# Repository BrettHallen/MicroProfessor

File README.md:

# Micro Professor MPF
The Multitech (Acer) Micro Professor MPF range of computers:

- MPF-I: Z80 trainer with six 7-digit display
- MPF-IA: Z80 trainer with six 7-digit display
- MPF-IB: Z80 trainer with six 7-digit display
- [MPF-IP: Z80 trainer with 20-digit VFD and QWERTY keyboard](/MPF-IP)
- MPF-I/88: 8088 trainer with 2x20 LCD
- MPF-II: 6502 Apple ][ clone with built-in keyboard
- [MPF-III: 6502 Apple //e clone with separate keyboard](/MPF-III)
- [MPF-PC/500: IBM PC/XT clone on an ISA card](/MPF-PC500)

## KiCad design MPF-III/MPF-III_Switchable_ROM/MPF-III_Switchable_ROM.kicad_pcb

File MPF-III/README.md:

# Multitech Micro Professor MPF-III
The MPF-III was Multitech's (later Acer) Apple //e clone, coming after the MPF-II Apple ][ clone.<br>

My example is a PAL model MPF-III/311.  The NTSC model is the MPF-III/310.<br>

Unfortunatley mine came without a keyboard which means it's not usable because:
- It's a custom keyboard using a serial protocol via a DE9 connector
- The schematics have been scrubbed from the Internet (Archive)
- You need a keyboard to do anything

I do know the DE9 interface pin out and am currently trying to reverse engineer the protocol.  I also know the scan codes and keyboard layout (but not keyboard matrix) from the available documentation.<br>

I do also have a dump of the MCS-48 firmware in the keyboard.<br>

My example actually has dual ROMs that can be switched: it has Multitech's original Apple clone firmware plus an almost exact copy of the Apple //e firmware.<br>

## [Documentation](/MPF-III/Documentation)
Copies of the MPF-III documentation (available on Archive) just in case they get disappeared from there:
- BASIC Programming Manual
- Operating Manual (working on trying to reduce my 190MB PDF copy)
- Reference Manual (working on trying to reduce my 190MB PDF copy)

## [Images](/MPF-III/Images)
Images of my MPF-III/311 machine's inards.

## [Keyboard](/MPF-III/Keyboard)
My in-progress attempt to develop a home brew replacement for the original Multitech keyboard.<br>

The keyboard looks to be similar to the Multitech AccuFeel so this is perhaps a possible replacment, if one of those could be found of course.

## [Switchable Firmware](/MPF-III/MPF-III_Switchable_ROM)
Small PCB to add the ability to switch between Multitech's original firmware (boots to "MPF-III") and the actual Apple //e firmware (boots to "APPLE ][".<br>

Takes two 27128 EPROMs (one for combined CD and one for combined EF) which are switched via the A13 address line.<br>

## [ROMs](/MPF-III/ROMs)
Dumps of the ROMs from my machine (MOS 1.3) and RetroAND's (MOS 1.1), plus also some analysis of the keyboard microcontroller code and maybe other parts that differ from a standard Apple IIe.<br>

A big thanks to [RetroAND and Retrolab](https://bitspassats.com/index.php/Main_Page) for getting the keyboard controller ROM dumped!

## [PALs](/MPF-III/PALs)
Dumps of the PALs courtesy of [RetroAND and Retrolab](https://bitspassats.com/index.php/Main_Page).

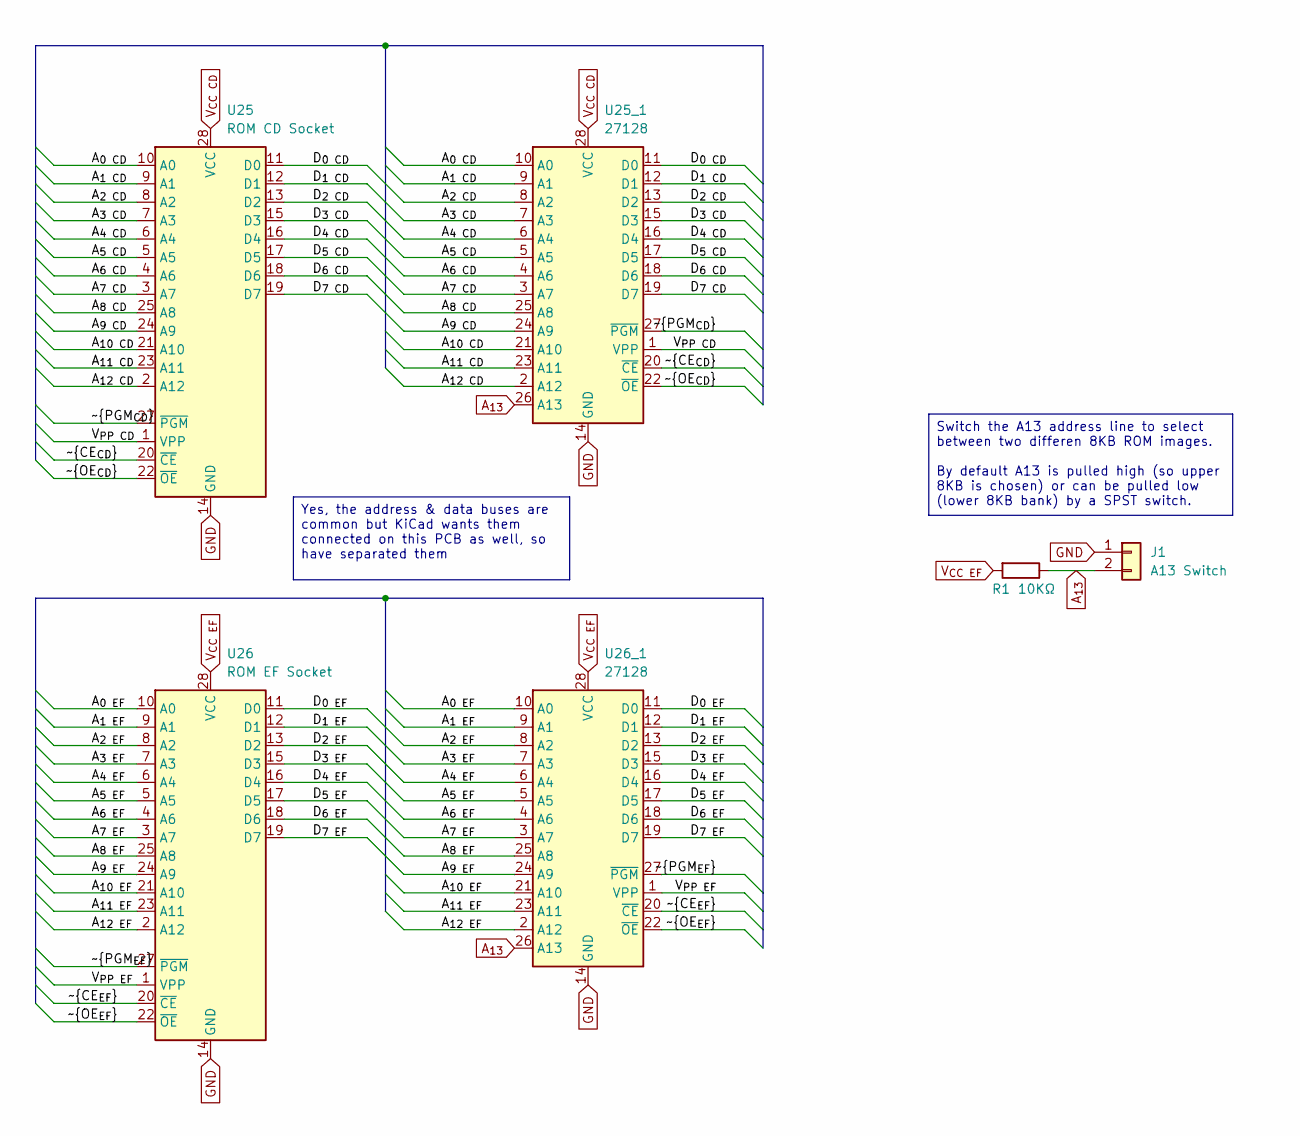
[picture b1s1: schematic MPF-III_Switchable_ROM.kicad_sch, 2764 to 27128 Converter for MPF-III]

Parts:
J1: A13 Switch; PinHeader_1x02_P2.54mm_Vertical
R1: 10KΩ; R_Axial_DIN0207_L6.3mm_D2.5mm_P7.62mm_Horizontal
U25: ROM CD Socket; DIP-28_Adapter
U25_1, U26_1: 27128; DIP-28_W15.24mm
U26: ROM EF Socket; DIP-28_Adapter

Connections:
/A_{0 CD}: U25.10 (A0), U25_1.10 (A0)
/A_{0 EF}: U26.10 (A0), U26_1.10 (A0)
/A_{1 CD}: U25.9 (A1), U25_1.9 (A1)
/A_{1 EF}: U26.9 (A1), U26_1.9 (A1)
/A_{2 CD}: U25.8 (A2), U25_1.8 (A2)
/A_{2 EF}: U26.8 (A2), U26_1.8 (A2)
/A_{3 CD}: U25.7 (A3), U25_1.7 (A3)
/A_{3 EF}: U26.7 (A3), U26_1.7 (A3)
/A_{4 CD}: U25.6 (A4), U25_1.6 (A4)
/A_{4 EF}: U26.6 (A4), U26_1.6 (A4)
/A_{5 CD}: U25.5 (A5), U25_1.5 (A5)
/A_{5 EF}: U26.5 (A5), U26_1.5 (A5)
/A_{6 CD}: U25.4 (A6), U25_1.4 (A6)
/A_{6 EF}: U26.4 (A6), U26_1.4 (A6)
/A_{7 CD}: U25.3 (A7), U25_1.3 (A7)
/A_{7 EF}: U26.3 (A7), U26_1.3 (A7)
/A_{8 CD}: U25.25 (A8), U25_1.25 (A8)
/A_{8 EF}: U26.25 (A8), U26_1.25 (A8)
/A_{9 CD}: U25.24 (A9), U25_1.24 (A9)
/A_{9 EF}: U26.24 (A9), U26_1.24 (A9)
/A_{10 CD}: U25.21 (A10), U25_1.21 (A10)
/A_{10 EF}: U26.21 (A10), U26_1.21 (A10)
/A_{11 CD}: U25.23 (A11), U25_1.23 (A11)
/A_{11 EF}: U26.23 (A11), U26_1.23 (A11)
/A_{12 CD}: U25.2 (A12), U25_1.2 (A12)
/A_{12 EF}: U26.2 (A12), U26_1.2 (A12)
/D_{0 CD}: U25.11 (D0), U25_1.11 (D0)
/D_{0 EF}: U26.11 (D0), U26_1.11 (D0)
/D_{1 CD}: U25.12 (D1), U25_1.12 (D1)
/D_{1 EF}: U26.12 (D1), U26_1.12 (D1)
/D_{2 CD}: U25.13 (D2), U25_1.13 (D2)
/D_{2 EF}: U26.13 (D2), U26_1.13 (D2)
/D_{3 CD}: U25.15 (D3), U25_1.15 (D3)
/D_{3 EF}: U26.15 (D3), U26_1.15 (D3)
/D_{4 CD}: U25.16 (D4), U25_1.16 (D4)
/D_{4 EF}: U26.16 (D4), U26_1.16 (D4)
/D_{5 CD}: U25.17 (D5), U25_1.17 (D5)
/D_{5 EF}: U26.17 (D5), U26_1.17 (D5)
/D_{6 CD}: U25.18 (D6), U25_1.18 (D6)
/D_{6 EF}: U26.18 (D6), U26_1.18 (D6)
/D_{7 CD}: U25.19 (D7), U25_1.19 (D7)
/D_{7 EF}: U26.19 (D7), U26_1.19 (D7)
/V_{PP CD}: U25.1 (VPP), U25_1.1 (VPP)
/V_{PP EF}: U26.1 (VPP), U26_1.1 (VPP)
/~CE_{CD}: U25.20 (~CE), U25_1.20 (~CE)
/~CE_{EF}: U26.20 (~CE), U26_1.20 (~CE)
/~OE_{CD}: U25.22 (~OE), U25_1.22 (~OE)
/~OE_{EF}: U26.22 (~OE), U26_1.22 (~OE)
/~PGM_{CD}: U25.27 (~PGM), U25_1.27 (~PGM)
/~PGM_{EF}: U26.27 (~PGM), U26_1.27 (~PGM)
A_{13}: J1.2, R1.1, U25_1.26 (A13), U26_1.26 (A13)
GND: J1.1, U25.14 (GND), U25_1.14 (GND), U26.14 (GND), U26_1.14 (GND)
V_{CC CD}: U25.28 (VCC), U25_1.28 (VCC)
V_{CC EF}: R1.2, U26.28 (VCC), U26_1.28 (VCC)

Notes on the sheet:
Switch the A13 address line to select between two differen 8KB ROM images. By default A13 is pulled high (so upper 8KB is chosen) or can be pulled low (lower 8KB bank) by a SPST switch.
Yes, the address & data buses are common but KiCad wants them connected on this PCB as well, so have separated them

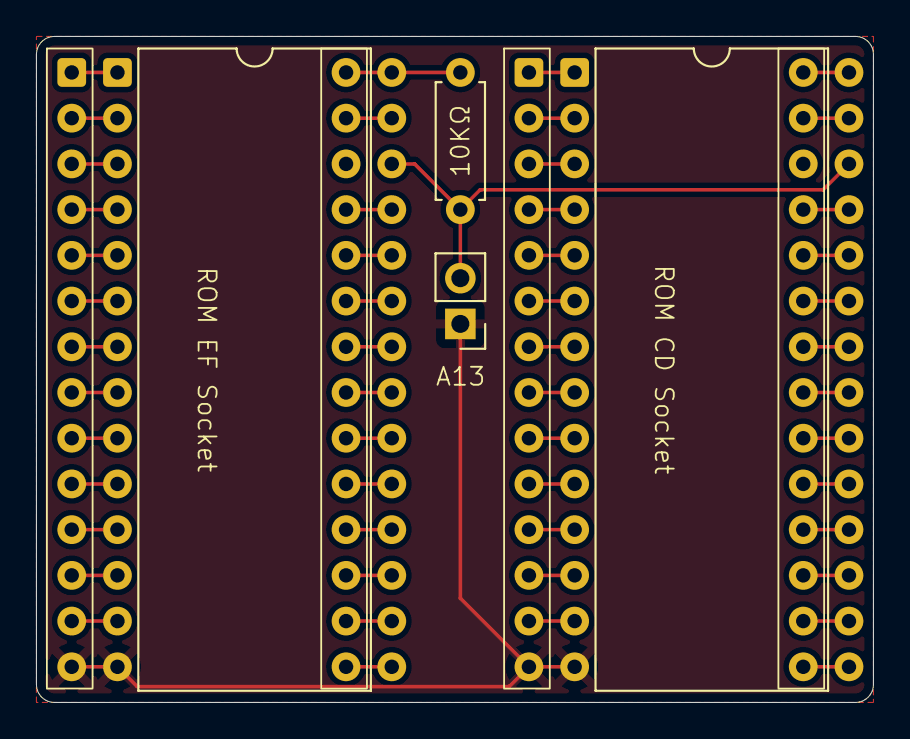
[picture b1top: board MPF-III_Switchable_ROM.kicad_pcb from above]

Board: 2 copper layers, 46.5 x 37.0 mm, 6 parts (0 on the bottom side), 54 nets.

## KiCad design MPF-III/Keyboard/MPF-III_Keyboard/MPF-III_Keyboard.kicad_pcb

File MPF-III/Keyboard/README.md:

# MPF-III Keyboard
Unfortunately my MPF-III came sans keyboard and there appears to be ZERO information about the keyboard controller (an Intel 8048) or its matrix layout, so I need to figure things out on my own.<br>

The MPF-III will execute a self-test if it boots without the presence of a keyboard.  (How is this detected?)<br>

This is what I've discovered - updating as I progress.<br>

## Keyboard Interface
We know it uses a serial protocol via the DE9 connector on the computer.  The pinout is known from documentation:

| DE9 Pin | Signal | MCU Pin                    |
|---------|--------|----------------------------|
| Pin 1   | PB1    |                            |
| Pin 2   | +5V    | 7 (EA), 26 (Vdd), 40 (Vcc) |
| Pin 3   | GND    | 20 (Vss)                   |
| Pin 4   | DATA   | 34 (P1.7)                  |
| Pin 5   | CLOCK  | 32 (P1.5)                  |
| Pin 6   | STROBE | 33 (P1.6)                  |
| Pin 7   | PB0    |                            |
| Pin 8   | RESET  |                            |
| Pin 9   | AKD    | 31 (P1.4)                  |

### PB0
To invoke a cold reset:
- Press CTRL + RESET then PB0
- Release CTRL + RESET then PB0
- The MPF-III will then perform a cold restart

### PB1
This key is used for self-test of the system:
- Press CTRL + RESET then PB1
- Release CTRL + RESET then PB1
- The MPF-III will then start the self-test (same as when computer boots with no keyboard connected)

### RESET
This is idle high.  To invoke a warm restart press CTRL + RESET.

### CLOCK
This signal is idle low.  The MPF takes this signal high when they keyboard takes AKD high.  It remains high as long as AKD is high.

### AKD (Any Key Down)
This signal is idle low.  The keyboard takes it high when a key is pressed.  In response the MPF will take the CLOCK high for the duration that AKD is high.<br>

### DATA
I'm guessing that the keyboard will send the scan code serially via the DATA signal and toggle the STROBE for each bit.  Under investigation.

### STROBE
I think ... maybe ... the keyboard will toggle STROBE for each scan code bit it sends serially via the DATA signal ... ?

## Keyboard microcontroller
Annotated disassembly of the MCS-48 code used by the controller is [here](https://github.com/BrettHallen/MicroProfessor/blob/main/MPF-III/ROMs/Analysis/MPF-III_KEYBOARD_disassembly.TXT) (thanks to RetroAND & his dad for making the ROM dump available!).<br>

## Keyboard matrix
Based on the controller disassembly, here is a possible keyboard matrix.  To be confirmed (because I don't have an actual keyboard!).

```
     Col7   Col6   Col5   Col4   Col3   Col2   Col1   Col0
    (bit7) (bit6) (bit5) (bit4) (bit3) (bit2) (bit1) (bit0)
   ┌───────────────────────────────────────────────────────┐
 R0│ F1     F2     F3     F4     F5     F6     F7     F8   │
   ├───────────────────────────────────────────────────────┤
 R1│ F9     F10    F11    F12    PB1    PB0    HALT   BREAK│
   ├───────────────────────────────────────────────────────┤
 R2│ ` ~    1 !    2 @    3 #    4 $    5 %    6 ^    7 &  │
   ├───────────────────────────────────────────────────────┤
 R3│ 8 *    9 (    0 )    - _    = +    \ |    DEL    INSC │
   ├───────────────────────────────────────────────────────┤
 R4│ Tab    Q      W      E      R      T      Y      U    │
   ├───────────────────────────────────────────────────────┤
 R5│ I      O      P      [ {    ] }           CPES   ←    │
   ├───────────────────────────────────────────────────────┤
 R6│ Caps   A      S      D      F      G      H      J    │
   ├───────────────────────────────────────────────────────┤
 R7│ K      L      ; :    ' "    Return CLRS   HOME   ↑    │
   ├───────────────────────────────────────────────────────┤
 R8│ Shift  Z      X      C      V      B      N      M    │
   ├───────────────────────────────────────────────────────┤
 R9│ , <    . >    / ?    Space  Ctrl   Alt    →      ↓    │
   ├───────────────────────────────────────────────────────┤
R10│NumLk  7 Home 8 ↑    9 PgUp  /      4 ←    5      6 →  │
   │ *     1 End  2 ↓    3 PgDn  -      0 Ins  . Del  + =  │
   └───────────────────────────────────────────────────────┘
```

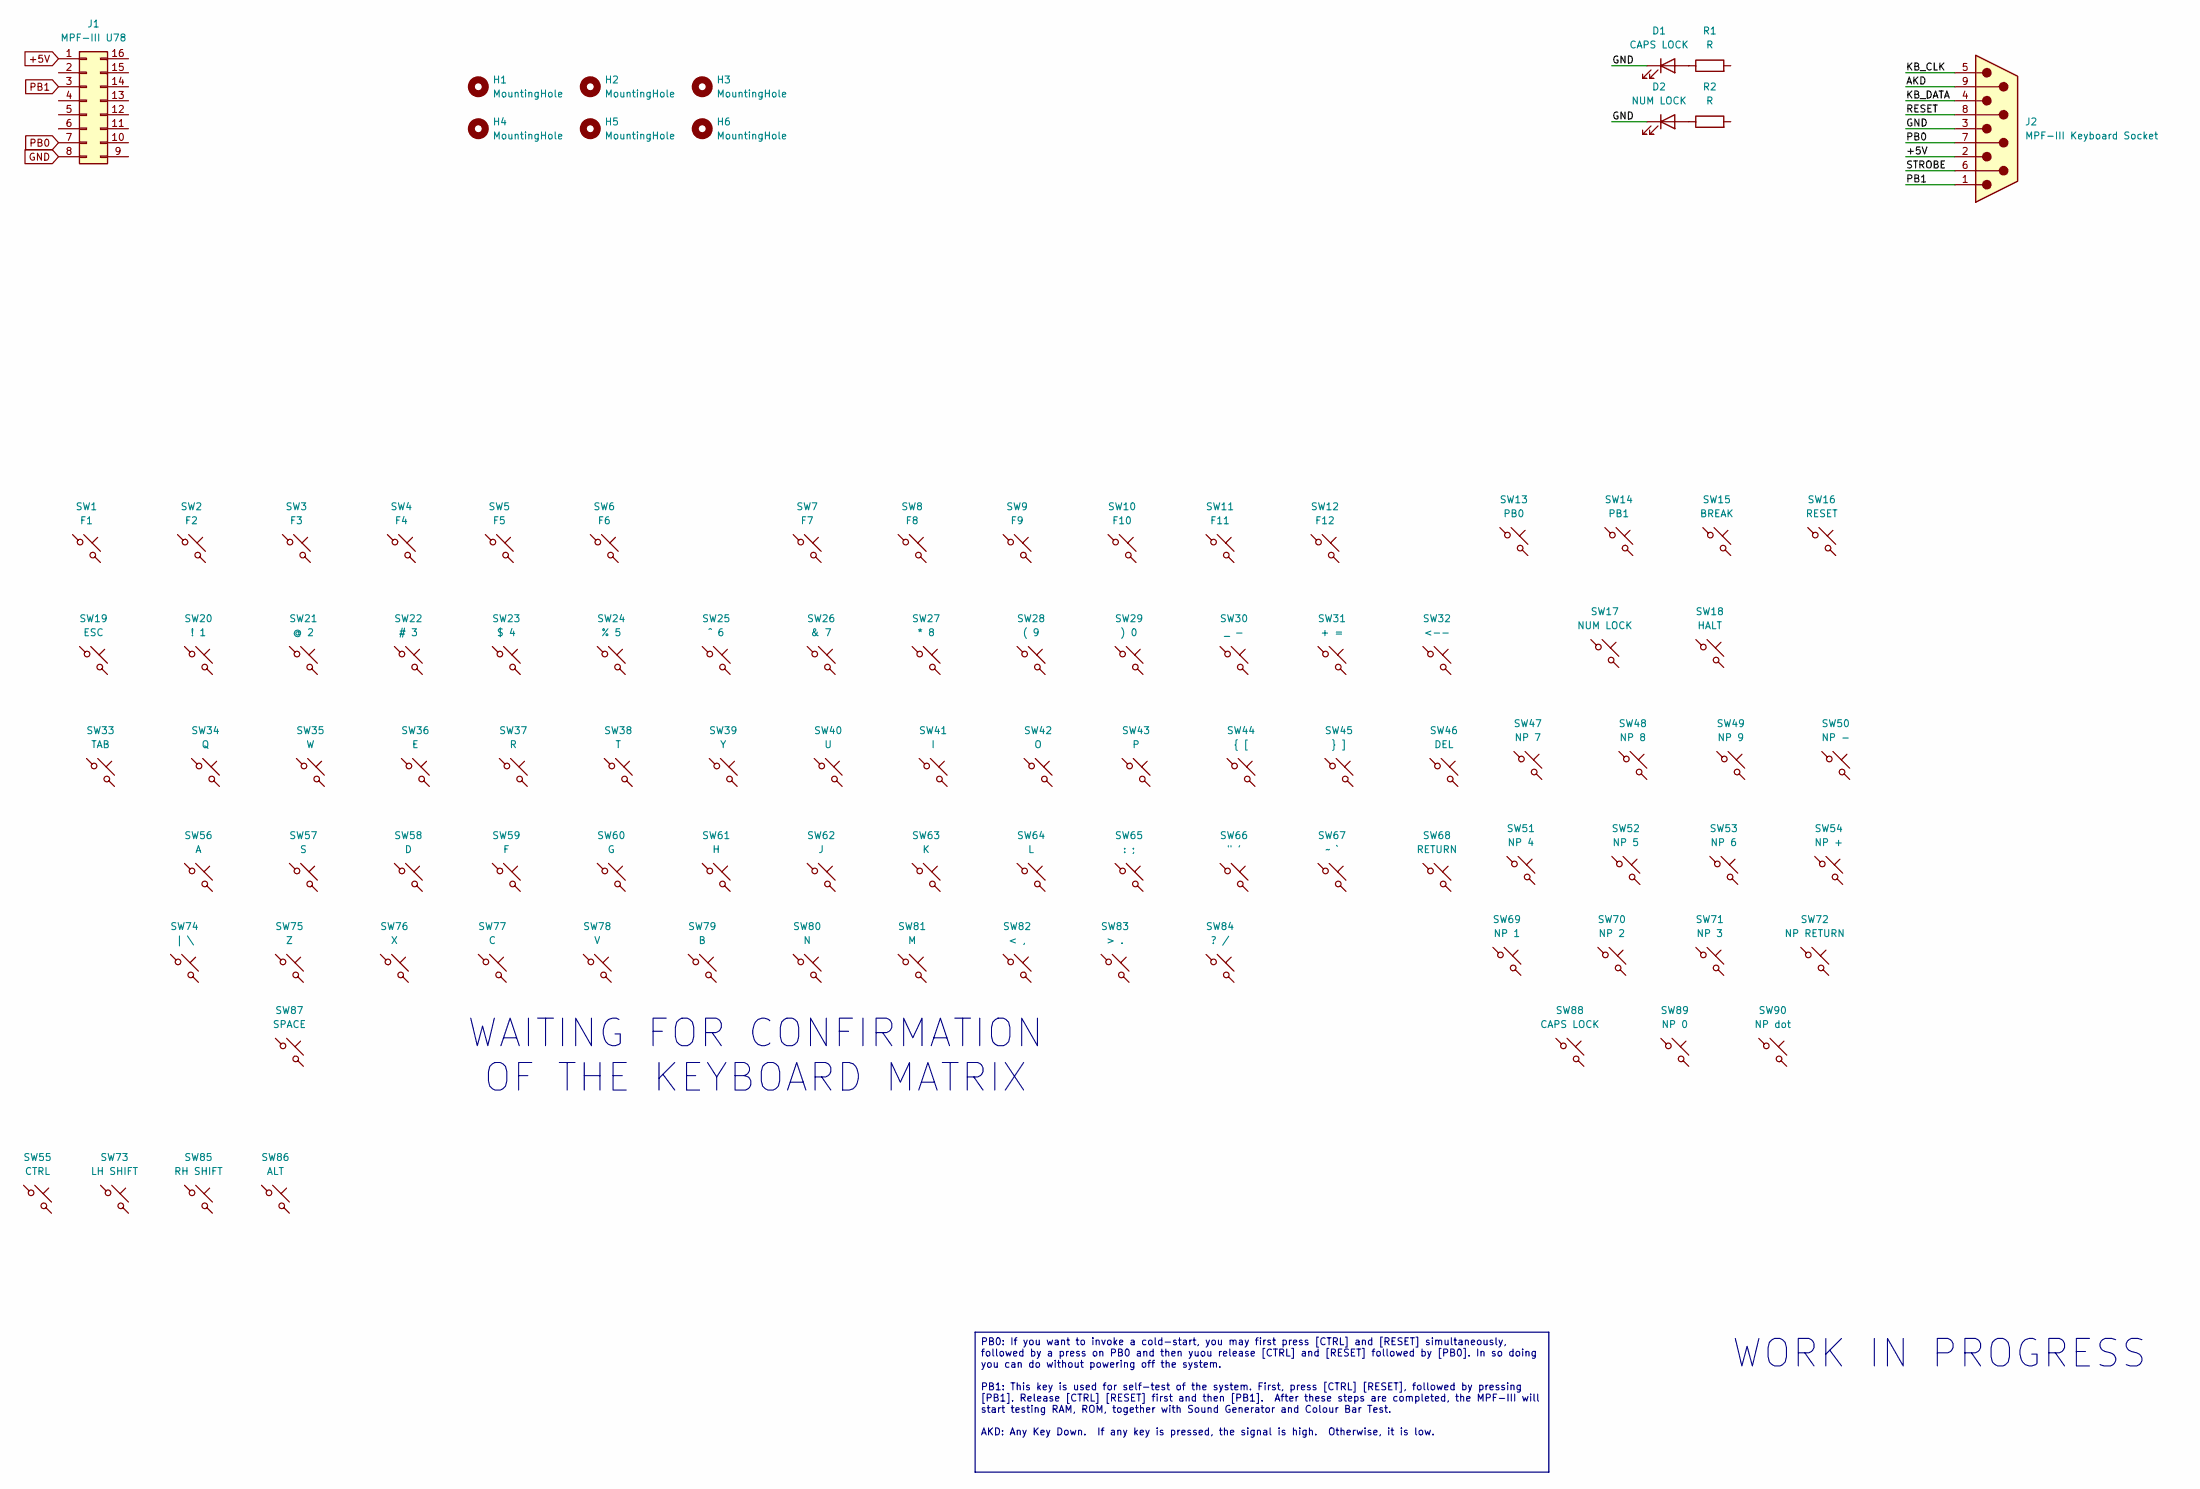
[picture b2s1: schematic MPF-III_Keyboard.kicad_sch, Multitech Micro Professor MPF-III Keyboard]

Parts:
D1: CAPS LOCK; LED_D5.0mm
D2: NUM LOCK; LED_D5.0mm
H1, H2, H3, H4, H5, H6: MountingHole; MountingHole_3.2mm_M3
J1: MPF-III U78
J2: MPF-III Keyboard Socket; DSUB-9_Pins_Horizontal_P2.77x2.84mm_EdgePinOffset7.70mm_Hou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
R1, R2: R; R_Axial_DIN0207_L6.3mm_D2.5mm_P10.16mm_Horizontal
SW1: F1; SW_Cherry_MX_PCB_1.00u
SW2: F2; SW_Cherry_MX_PCB_1.00u
SW3: F3; SW_Cherry_MX_PCB_1.00u
SW4: F4; SW_Cherry_MX_PCB_1.00u
SW5: F5; SW_Cherry_MX_PCB_1.00u
SW6: F6; SW_Cherry_MX_PCB_1.00u
SW7: F7; SW_Cherry_MX_PCB_1.00u
SW8: F8; SW_Cherry_MX_PCB_1.00u
SW9: F9; SW_Cherry_MX_PCB_1.00u
SW10: F10; SW_Cherry_MX_PCB_1.00u
SW11: F11; SW_Cherry_MX_PCB_1.00u
SW12: F12; SW_Cherry_MX_PCB_1.00u
SW13: PB0; SW_Cherry_MX_PCB_1.00u
SW14: PB1; SW_Cherry_MX_PCB_1.00u
SW15: BREAK; SW_Cherry_MX_PCB_1.00u
SW16: RESET; SW_Cherry_MX_PCB_1.00u
SW17: NUM LOCK; SW_Cherry_MX_PCB_2.00u
SW18: HALT; SW_Cherry_MX_PCB_2.00u
SW19: ESC; SW_Cherry_MX_PCB_1.00u
SW20: ! 1; SW_Cherry_MX_PCB_1.00u
SW21: @ 2; SW_Cherry_MX_PCB_1.00u
SW22: # 3; SW_Cherry_MX_PCB_1.00u
SW23: $ 4; SW_Cherry_MX_PCB_1.00u
SW24: % 5; SW_Cherry_MX_PCB_1.00u
SW25: ^ 6; SW_Cherry_MX_PCB_1.00u
SW26: & 7; SW_Cherry_MX_PCB_1.00u
SW27: * 8; SW_Cherry_MX_PCB_1.00u
SW28: ( 9; SW_Cherry_MX_PCB_1.00u
SW29: ) 0; SW_Cherry_MX_PCB_1.00u
SW30: _ -; SW_Cherry_MX_PCB_1.00u
SW31: + =; SW_Cherry_MX_PCB_1.00u
SW32: <--; SW_Cherry_MX_PCB_2.00u
SW33: TAB; SW_Cherry_MX_PCB_1.50u
SW34: Q; SW_Cherry_MX_PCB_1.00u
SW35: W; SW_Cherry_MX_PCB_1.00u
SW36: E; SW_Cherry_MX_PCB_1.00u
SW37: R; SW_Cherry_MX_PCB_1.00u
SW38: T; SW_Cherry_MX_PCB_1.00u
SW39: Y; SW_Cherry_MX_PCB_1.00u
SW40: U; SW_Cherry_MX_PCB_1.00u
SW41: I; SW_Cherry_MX_PCB_1.00u
SW42: O; SW_Cherry_MX_PCB_1.00u
SW43: P; SW_Cherry_MX_PCB_1.00u
SW44: { [; SW_Cherry_MX_PCB_1.00u
SW45: } ]; SW_Cherry_MX_PCB_1.00u
SW46: DEL; SW_Cherry_MX_PCB_1.50u
SW47: NP 7; SW_Cherry_MX_PCB_1.00u
SW48: NP 8; SW_Cherry_MX_PCB_1.00u
SW49: NP 9; SW_Cherry_MX_PCB_1.00u
SW50: NP -; SW_Cherry_MX_PCB_1.00u
SW51: NP 4; SW_Cherry_MX_PCB_1.00u
SW52: NP 5; SW_Cherry_MX_PCB_1.00u
SW53: NP 6; SW_Cherry_MX_PCB_1.00u
SW54: NP +; SW_Cherry_MX_PCB_1.00u
SW55: CTRL; SW_Cherry_MX_PCB_2.00u
SW56: A; SW_Cherry_MX_PCB_1.00u
SW57: S; SW_Cherry_MX_PCB_1.00u
SW58: D; SW_Cherry_MX_PCB_1.00u
SW59: F; SW_Cherry_MX_PCB_1.00u
SW60: G; SW_Cherry_MX_PCB_1.00u
SW61: H; SW_Cherry_MX_PCB_1.00u
SW62: J; SW_Cherry_MX_PCB_1.00u
SW63: K; SW_Cherry_MX_PCB_1.00u
SW64: L; SW_Cherry_MX_PCB_1.00u
SW65: : ;; SW_Cherry_MX_PCB_1.00u
SW66: " '; SW_Cherry_MX_PCB_1.00u
SW67: ~ `; SW_Cherry_MX_PCB_1.00u
SW68: RETURN; SW_Cherry_MX_PCB_2.00u_90deg
SW69: NP 1; SW_Cherry_MX_PCB_1.00u
SW70: NP 2; SW_Cherry_MX_PCB_1.00u
SW71: NP 3; SW_Cherry_MX_PCB_1.00u
SW72: NP RETURN; SW_Cherry_MX_PCB_2.00u_90deg
SW73: LH SHIFT; SW_Cherry_MX_PCB_1.50u
SW74: | \; SW_Cherry_MX_PCB_1.00u
SW75: Z; SW_Cherry_MX_PCB_1.00u
SW76: X; SW_Cherry_MX_PCB_1.00u
SW77: C; SW_Cherry_MX_PCB_1.00u
SW78: V; SW_Cherry_MX_PCB_1.00u
SW79: B; SW_Cherry_MX_PCB_1.00u
SW80: N; SW_Cherry_MX_PCB_1.00u
SW81: M; SW_Cherry_MX_PCB_1.00u
SW82: < ,; SW_Cherry_MX_PCB_1.00u
SW83: > .; SW_Cherry_MX_PCB_1.00u
SW84: ? /; SW_Cherry_MX_PCB_1.00u
SW85: RH SHIFT; SW_Cherry_MX_PCB_1.50u
SW86: ALT; SW_Cherry_MX_PCB_2.25u
SW87: SPACE; SW_Cherry_MX_PCB_7.00u
SW88: CAPS LOCK; SW_Cherry_MX_PCB_2.00u
SW89: NP 0; SW_Cherry_MX_PCB_2.00u
SW90: NP dot; SW_Cherry_MX_PCB_2.00u

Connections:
+5V: J2.2
/AKD: J2.9
/KB_CLK: J2.5
/KB_DATA: J2.4
/RESET: J2.8
/STROBE: J2.6
GND: D1.1 (K), D2.1 (K), J2.3
unnamed: D1.2 (A), R1.1
unnamed: D2.2 (A), R2.1
PB0: J2.7
PB1: J2.1

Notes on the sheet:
WORK IN PROGRESS
WAITING FOR CONFIRMATION OF THE KEYBOARD MATRIX
PB0: If you want to invoke a cold-start, you may first press [CTRL] and [RESET] simultaneously, followed by a press on PB0 and then yuou release [CTRL] and [RESET] followed by [PB0]. In so doing you can do without powering off the system. PB1: This key is used for self-test of the system. First, pr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

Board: 2 copper layers, 101 parts (0 on the bottom side), 3 nets, no tracks yet.

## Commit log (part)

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2025-11-23 Moved to Converter Boards repository
2025-11-26 Combined ROMs
2025-11-29 Designed keyboard layout
2025-12-02 Started PCB layout
2026-01-24 Added CRC32 checksums to filenames
2026-01-24 Added ROM size to filename
2026-01-24 Helper Python scripts for ROM analysis
    [1] Dump possible text strings to ASCII
    [2] Calculate ROM checksum as per original self-test
2026-01-24 Replaced corrupt EF#2 dump with original IIe dump
2026-01-24 Start keyboard MCU analysis
2026-01-25 Added documentation
2026-01-25 Initial keyboard firmware analysis
2026-01-25 Possible key matrix layout
2026-01-25 Added CRC32 chhecksums
2026-01-25 Moved combined ROMs to own folder
2026-01-25 Added PAL sub-title
2026-01-25 Initial commit of PAL dumps
2026-01-25 Reorganise/rename ROM dumps
2026-01-25 Filename updates
2026-01-26 Cosmetic changes
2026-01-27 Missing pages, removed
2026-01-27 Revised PCB layout -> Rev. B
2026-06-19 PCB images
    Thanks to RetroAND!
2026-06-19 Annoted disassembly of keyboard firmware
    Thanks to Claude Code, disassembly of the 8035/MCS-48 firmware in the keyboard.
    Required to reverse engineer a replacement keyboard.
2026-06-19 Keyboard matrix from firmware
2026-06-19 Keyboard matrix
    Finally!
2026-06-19 Claude Code analysis
    Outputs from Uncle Claude's keyboard firmware (8035/MCS-48) analysis
2026-06-22 Prints the letter "A"
2026-06-22 Claude analysis of keyboard protocol
